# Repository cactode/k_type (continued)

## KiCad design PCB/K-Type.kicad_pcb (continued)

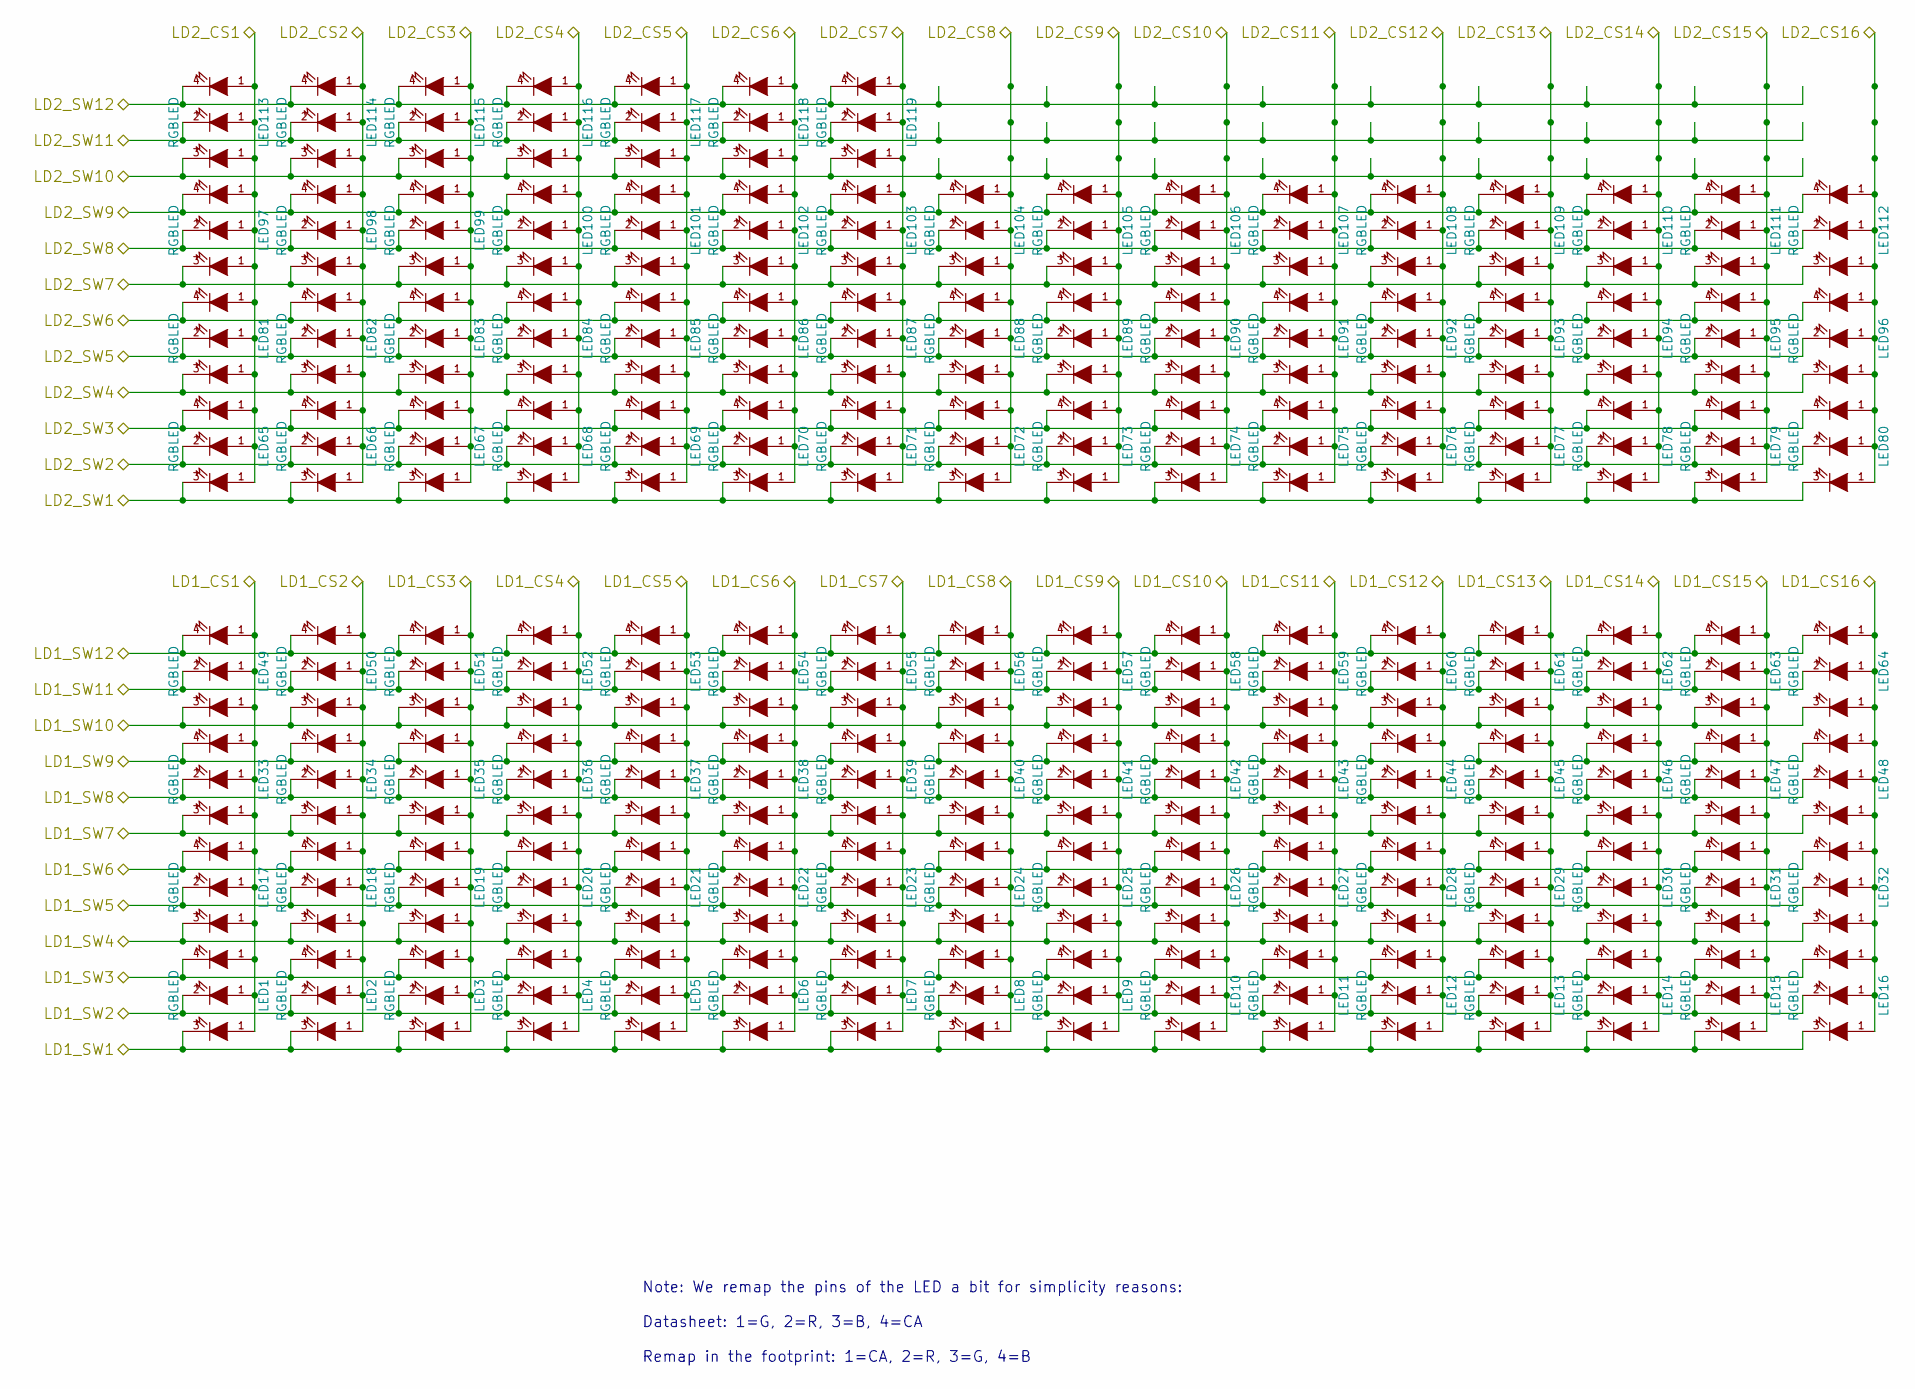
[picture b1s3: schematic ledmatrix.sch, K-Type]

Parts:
LED1, LED2, LED3, LED4, LED5, LED6, LED7, LED8, LED9, LED10, LED11, LED12, LED13, LED14, LED15, LED16, LED17, LED18, LED19, LED20, LED21, LED22, LED23, LED24, LED25, LED26, LED27, LED28, LED29, LED30, LED31, LED32, LED33, LED34, LED35, LED36, LED37, LED38, LED39, LED40, LED41, LED42, LED43, LED44, LED45, LED46, LED47, LED48, LED49, LED50, LED51, LED52, LED53, LED54, LED55, LED56, LED57, LED58, LED59, LED60, LED61, LED62, LED63, LED64, LED65, LED66, LED67, LED68, LED69, LED70, LED71, LED72, LED73, LED74, LED75, LED76, LED77, LED78, LED79, LED80, LED81, LED82, LED83, LED84, LED85, LED86, LED87: RGBLED; LED_RGB_3.2x2.8_REVMOUNT
LED88, LED89, LED90, LED91, LED92, LED93, LED94, LED95, LED96, LED97, LED98, LED99, LED100, LED101, LED102, LED103, LED104, LED105, LED106, LED107, LED108, LED109, LED110, LED111, LED112, LED113, LED114, LED115, LED116, LED117, LED118, LED119: RGBLED; LED_RGB_3.2x2.8_REVMOUNT_BACKWARDS

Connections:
/ledmatrix/LD1_CS1: LED1.1 (A), LED17.1 (A), LED33.1 (A), LED49.1 (A); also elsewhere on the board
/ledmatrix/LD1_CS2: LED2.1 (A), LED18.1 (A), LED34.1 (A), LED50.1 (A); also elsewhere on the board
/ledmatrix/LD1_CS3: LED3.1 (A), LED19.1 (A), LED35.1 (A), LED51.1 (A); also elsewhere on the board
/ledmatrix/LD1_CS4: LED4.1 (A), LED20.1 (A), LED36.1 (A), LED52.1 (A); also elsewhere on the board
/ledmatrix/LD1_CS5: LED5.1 (A), LED21.1 (A), LED37.1 (A), LED53.1 (A); also elsewhere on the board
/ledmatrix/LD1_CS6: LED6.1 (A), LED22.1 (A), LED38.1 (A), LED54.1 (A); also elsewhere on the board
/ledmatrix/LD1_CS7: LED7.1 (A), LED23.1 (A), LED39.1 (A), LED55.1 (A); also elsewhere on the board
/ledmatrix/LD1_CS8: LED8.1 (A), LED24.1 (A), LED40.1 (A), LED56.1 (A); also elsewhere on the board
/ledmatrix/LD1_CS9: LED9.1 (A), LED25.1 (A), LED41.1 (A), LED57.1 (A); also elsewhere on the board
/ledmatrix/LD1_CS10: LED10.1 (A), LED26.1 (A), LED42.1 (A), LED58.1 (A); also elsewhere on the board
/ledmatrix/LD1_CS11: LED11.1 (A), LED27.1 (A), LED43.1 (A), LED59.1 (A); also elsewhere on the board
/ledmatrix/LD1_CS12: LED12.1 (A), LED28.1 (A), LED44.1 (A), LED60.1 (A); also elsewhere on the board
/ledmatrix/LD1_CS13: LED13.1 (A), LED29.1 (A), LED45.1 (A), LED61.1 (A); also elsewhere on the board
/ledmatrix/LD1_CS14: LED14.1 (A), LED30.1 (A), LED46.1 (A), LED62.1 (A); also elsewhere on the board
/ledmatrix/LD1_CS15: LED15.1 (A), LED31.1 (A), LED47.1 (A), LED63.1 (A); also elsewhere on the board
/ledmatrix/LD1_CS16: LED16.1 (A), LED32.1 (A), LED48.1 (A), LED64.1 (A); also elsewhere on the board
/ledmatrix/LD1_SW1: LED1.3 (G), LED2.3 (G), LED3.3 (G), LED4.3 (G), LED5.3 (G), LED6.3 (G), LED7.3 (G), LED8.3 (G), LED9.3 (G), LED10.3 (G), LED11.3 (G), LED12.3 (G), LED13.3 (G), LED14.3 (G), LED15.3 (G), LED16.3 (G); also elsewhere on the board
/ledmatrix/LD1_SW2: LED1.2 (R), LED2.2 (R), LED3.2 (R), LED4.2 (R), LED5.2 (R), LED6.2 (R), LED7.2 (R), LED8.2 (R), LED9.2 (R), LED10.2 (R), LED11.2 (R), LED12.2 (R), LED13.2 (R), LED14.2 (R), LED15.2 (R), LED16.2 (R); also elsewhere on the board
/ledmatrix/LD1_SW3: LED1.4 (B), LED2.4 (B), LED3.4 (B), LED4.4 (B), LED5.4 (B), LED6.4 (B), LED7.4 (B), LED8.4 (B), LED9.4 (B), LED10.4 (B), LED11.4 (B), LED12.4 (B), LED13.4 (B), LED14.4 (B), LED15.4 (B), LED16.4 (B); also elsewhere on the board
/ledmatrix/LD1_SW4: LED17.3 (G), LED18.3 (G), LED19.3 (G), LED20.3 (G), LED21.3 (G), LED22.3 (G), LED23.3 (G), LED24.3 (G), LED25.3 (G), LED26.3 (G), LED27.3 (G), LED28.3 (G), LED29.3 (G), LED30.3 (G), LED31.3 (G), LED32.3 (G); also elsewhere on the board
/ledmatrix/LD1_SW5: LED17.2 (R), LED18.2 (R), LED19.2 (R), LED20.2 (R), LED21.2 (R), LED22.2 (R), LED23.2 (R), LED24.2 (R), LED25.2 (R), LED26.2 (R), LED27.2 (R), LED28.2 (R), LED29.2 (R), LED30.2 (R), LED31.2 (R), LED32.2 (R); also elsewhere on the board
/ledmatrix/LD1_SW6: LED17.4 (B), LED18.4 (B), LED19.4 (B), LED20.4 (B), LED21.4 (B), LED22.4 (B), LED23.4 (B), LED24.4 (B), LED25.4 (B), LED26.4 (B), LED27.4 (B), LED28.4 (B), LED29.4 (B), LED30.4 (B), LED31.4 (B), LED32.4 (B); also elsewhere on the board
/ledmatrix/LD1_SW7: LED33.3 (G), LED34.3 (G), LED35.3 (G), LED36.3 (G), LED37.3 (G), LED38.3 (G), LED39.3 (G), LED40.3 (G), LED41.3 (G), LED42.3 (G), LED43.3 (G), LED44.3 (G), LED45.3 (G), LED46.3 (G), LED47.3 (G), LED48.3 (G); also elsewhere on the board
/ledmatrix/LD1_SW8: LED33.2 (R), LED34.2 (R), LED35.2 (R), LED36.2 (R), LED37.2 (R), LED38.2 (R), LED39.2 (R), LED40.2 (R), LED41.2 (R), LED42.2 (R), LED43.2 (R), LED44.2 (R), LED45.2 (R), LED46.2 (R), LED47.2 (R), LED48.2 (R); also elsewhere on the board
/ledmatrix/LD1_SW9: LED33.4 (B), LED34.4 (B), LED35.4 (B), LED36.4 (B), LED37.4 (B), LED38.4 (B), LED39.4 (B), LED40.4 (B), LED41.4 (B), LED42.4 (B), LED43.4 (B), LED44.4 (B), LED45.4 (B), LED46.4 (B), LED47.4 (B), LED48.4 (B); also elsewhere on the board
/ledmatrix/LD1_SW10: LED49.3 (G), LED50.3 (G), LED51.3 (G), LED52.3 (G), LED53.3 (G), LED54.3 (G), LED55.3 (G), LED56.3 (G), LED57.3 (G), LED58.3 (G), LED59.3 (G), LED60.3 (G), LED61.3 (G), LED62.3 (G), LED63.3 (G), LED64.3 (G); also elsewhere on the board
/ledmatrix/LD1_SW11: LED49.2 (R), LED50.2 (R), LED51.2 (R), LED52.2 (R), LED53.2 (R), LED54.2 (R), LED55.2 (R), LED56.2 (R), LED57.2 (R), LED58.2 (R), LED59.2 (R), LED60.2 (R), LED61.2 (R), LED62.2 (R), LED63.2 (R), LED64.2 (R); also elsewhere on the board
/ledmatrix/LD1_SW12: LED49.4 (B), LED50.4 (B), LED51.4 (B), LED52.4 (B), LED53.4 (B), LED54.4 (B), LED55.4 (B), LED56.4 (B), LED57.4 (B), LED58.4 (B), LED59.4 (B), LED60.4 (B), LED61.4 (B), LED62.4 (B), LED63.4 (B), LED64.4 (B); also elsewhere on the board
/ledmatrix/LD2_CS1: LED65.1 (A), LED81.1 (A), LED97.1 (A), LED113.1 (A); also elsewhere on the board
/ledmatrix/LD2_CS2: LED66.1 (A), LED82.1 (A), LED98.1 (A), LED114.1 (A); also elsewhere on the board
/ledmatrix/LD2_CS3: LED67.1 (A), LED83.1 (A), LED99.1 (A), LED115.1 (A); also elsewhere on the board
/ledmatrix/LD2_CS4: LED68.1 (A), LED84.1 (A), LED100.1 (A), LED116.1 (A); also elsewhere on the board
/ledmatrix/LD2_CS5: LED69.1 (A), LED85.1 (A), LED101.1 (A), LED117.1 (A); also elsewhere on the board
/ledmatrix/LD2_CS6: LED70.1 (A), LED86.1 (A), LED102.1 (A), LED118.1 (A); also elsewhere on the board
/ledmatrix/LD2_CS7: LED71.1 (A), LED87.1 (A), LED103.1 (A), LED119.1 (A); also elsewhere on the board
/ledmatrix/LD2_CS8: LED72.1 (A), LED88.1 (A), LED104.1 (A); also elsewhere on the board
/ledmatrix/LD2_CS9: LED73.1 (A), LED89.1 (A), LED105.1 (A); also elsewhere on the board
/ledmatrix/LD2_CS10: LED74.1 (A), LED90.1 (A), LED106.1 (A); also elsewhere on the board
/ledmatrix/LD2_CS11: LED75.1 (A), LED91.1 (A), LED107.1 (A); also elsewhere on the board
/ledmatrix/LD2_CS12: LED76.1 (A), LED92.1 (A), LED108.1 (A); also elsewhere on the board
/ledmatrix/LD2_CS13: LED77.1 (A), LED93.1 (A), LED109.1 (A); also elsewhere on the board
/ledmatrix/LD2_CS14: LED78.1 (A), LED94.1 (A), LED110.1 (A); also elsewhere on the board
/ledmatrix/LD2_CS15: LED79.1 (A), LED95.1 (A), LED111.1 (A); also elsewhere on the board
/ledmatrix/LD2_CS16: LED80.1 (A), LED96.1 (A), LED112.1 (A); also elsewhere on the board
/ledmatrix/LD2_SW1: LED65.3 (G), LED66.3 (G), LED67.3 (G), LED68.3 (G), LED69.3 (G), LED70.3 (G), LED71.3 (G), LED72.3 (G), LED73.3 (G), LED74.3 (G), LED75.3 (G), LED76.3 (G), LED77.3 (G), LED78.3 (G), LED79.3 (G), LED80.3 (G); also elsewhere on the board
/ledmatrix/LD2_SW2: LED65.2 (R), LED66.2 (R), LED67.2 (R), LED68.2 (R), LED69.2 (R), LED70.2 (R), LED71.2 (R), LED72.2 (R), LED73.2 (R), LED74.2 (R), LED75.2 (R), LED76.2 (R), LED77.2 (R), LED78.2 (R), LED79.2 (R), LED80.2 (R); also elsewhere on the board
/ledmatrix/LD2_SW3: LED65.4 (B), LED66.4 (B), LED67.4 (B), LED68.4 (B), LED69.4 (B), LED70.4 (B), LED71.4 (B), LED72.4 (B), LED73.4 (B), LED74.4 (B), LED75.4 (B), LED76.4 (B), LED77.4 (B), LED78.4 (B), LED79.4 (B), LED80.4 (B); also elsewhere on the board
/ledmatrix/LD2_SW4: LED81.3 (G), LED82.3 (G), LED83.3 (G), LED84.3 (G), LED85.3 (G), LED86.3 (G), LED87.3 (G), LED88.3 (G), LED89.3 (G), LED90.3 (G), LED91.3 (G), LED92.3 (G), LED93.3 (G), LED94.3 (G), LED95.3 (G), LED96.3 (G); also elsewhere on the board
/ledmatrix/LD2_SW5: LED81.2 (R), LED82.2 (R), LED83.2 (R), LED84.2 (R), LED85.2 (R), LED86.2 (R), LED87.2 (R), LED88.2 (R), LED89.2 (R), LED90.2 (R), LED91.2 (R), LED92.2 (R), LED93.2 (R), LED94.2 (R), LED95.2 (R), LED96.2 (R); also elsewhere on the board
/ledmatrix/LD2_SW6: LED81.4 (B), LED82.4 (B), LED83.4 (B), LED84.4 (B), LED85.4 (B), LED86.4 (B), LED87.4 (B), LED88.4 (B), LED89.4 (B), LED90.4 (B), LED91.4 (B), LED92.4 (B), LED93.4 (B), LED94.4 (B), LED95.4 (B), LED96.4 (B); also elsewhere on the board
/ledmatrix/LD2_SW7: LED97.3 (G), LED98.3 (G), LED99.3 (G), LED100.3 (G), LED101.3 (G), LED102.3 (G), LED103.3 (G), LED104.3 (G), LED105.3 (G), LED106.3 (G), LED107.3 (G), LED108.3 (G), LED109.3 (G), LED110.3 (G), LED111.3 (G), LED112.3 (G); also elsewhere on the board
/ledmatrix/LD2_SW8: LED97.2 (R), LED98.2 (R), LED99.2 (R), LED100.2 (R), LED101.2 (R), LED102.2 (R), LED103.2 (R), LED104.2 (R), LED105.2 (R), LED106.2 (R), LED107.2 (R), LED108.2 (R), LED109.2 (R), LED110.2 (R), LED111.2 (R), LED112.2 (R); also elsewhere on the board
/ledmatrix/LD2_SW9: LED97.4 (B), LED98.4 (B), LED99.4 (B), LED100.4 (B), LED101.4 (B), LED102.4 (B), LED103.4 (B), LED104.4 (B), LED105.4 (B), LED106.4 (B), LED107.4 (B), LED108.4 (B), LED109.4 (B), LED110.4 (B), LED111.4 (B), LED112.4 (B); also elsewhere on the board
/ledmatrix/LD2_SW10: LED113.3 (G), LED114.3 (G), LED115.3 (G), LED116.3 (G), LED117.3 (G), LED118.3 (G), LED119.3 (G); also elsewhere on the board
/ledmatrix/LD2_SW11: LED113.2 (R), LED114.2 (R), LED115.2 (R), LED116.2 (R), LED117.2 (R), LED118.2 (R), LED119.2 (R); also elsewhere on the board
/ledmatrix/LD2_SW12: LED113.4 (B), LED114.4 (B), LED115.4 (B), LED116.4 (B), LED117.4 (B), LED118.4 (B), LED119.4 (B); also elsewhere on the board

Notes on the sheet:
Note: We remap the pins of the LED a bit for simplicity reasons: Datasheet: 1=G, 2=R, 3=B, 4=CA Remap in the footprint: 1=CA, 2=R, 3=G, 4=B

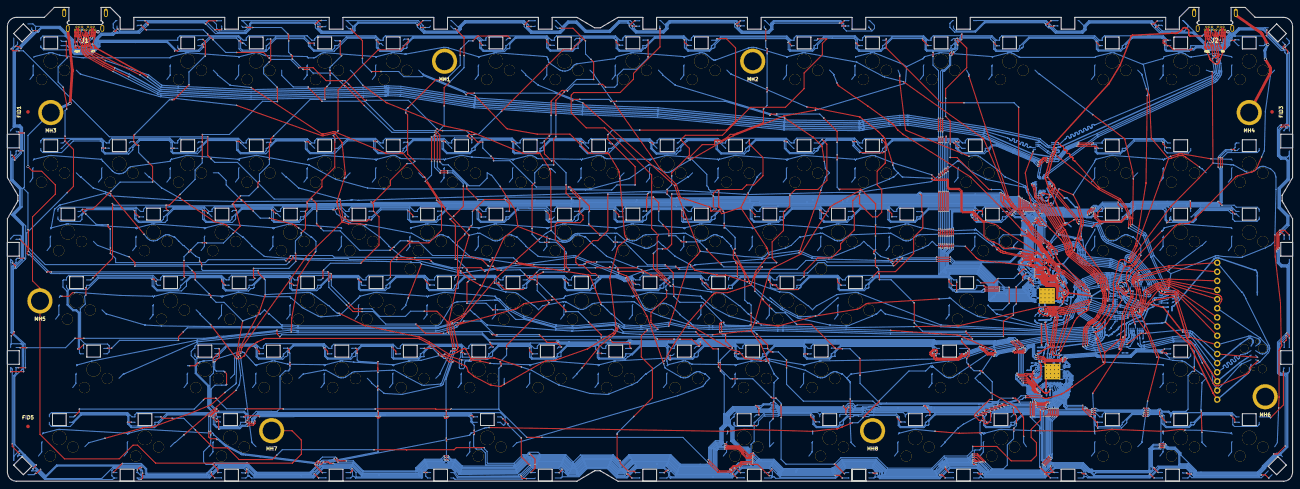
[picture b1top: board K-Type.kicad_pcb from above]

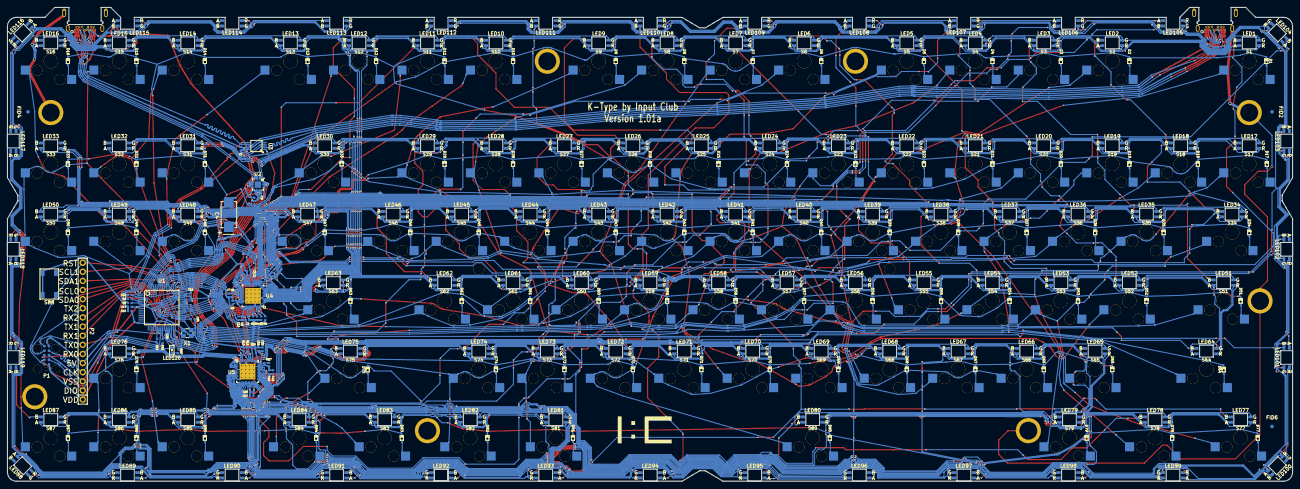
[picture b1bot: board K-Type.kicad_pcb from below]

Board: 2 copper layers, 357.5 x 131.8 mm, 362 parts (256 on the bottom side), 210 nets.

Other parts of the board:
FID1, FID2, FID3, FID4, FID5, FID6: >VALUE; FID
IC_LOGO: IC_LOGO
TH1, TH2: 1PAD; 1PAD-NPTH-SMALL

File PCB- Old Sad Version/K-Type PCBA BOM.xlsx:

# | Qty | Part Reference | Part Number | MFGR | Description | Footprint | Notes
1 | 12 | C5,C8,C11,C20,C23,C12,C2,C6,C9,C16,C18,C21 | EMK105B7104KV-F | Taiyo Yuden | Multilayer Ceramic Capacitors MLCC - SMD/SMT .1uF 16Volts X7R +/-10% 0402 STD | SMD-0402 | https://www.digikey.com/product-detail/en/EMK105B7104KV-F/58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
2 | 8 | C1,C3,C7,C10,C15,C17,C19,C22 | JMK105BJ474KV-F | Taiyo Yuden | Multilayer Ceramic Capacitors MLCC - SMD/SMT 0.47uF 6.3V X5R +/-10% 0402 Gen Pu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 | SMD-0402 | https://www.digikey.com/product-detail/en/JMK105BJ474KV-F/58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
3 | 1 | C4 | EEF-CX1D220R | Panasonic | Aluminum Organic Polymer Capacitors 22uF 20volt SP-Cap AEC-Q200 | SMD-7343-Pol | https://www.digikey.com/product-detail/en/EEF-CX1D220R/P1899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
4 | 2 | C14,C13 | JMK105C6225MV-F | Taiyo Yuden | Multilayer Ceramic Capacitors MLCC - SMD/SMT 2.2uF 6.3Volts X6S +/-20% 0402 STD | SMD-0402 | https://www.digikey.com/product-detail/en/taiyo-yuden/JMK105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
5 | 87 | D1..D87 | 1N4148X-TP | MCC | Diodes - General Purpose, Power, Switching 150mA 75V | SOD-523 | https://www.digikey.com/product-detail/en/1N4148X-TP/1N4148X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
6 | 2 | J2,J1 | DX07B024XJ1R1300 | JAE Electronics | USB Connectors HYBRID SMT/THRU-HOLE MID MNT - USB TYPE C | USB_C_MIDMOUNT_TH_IMPCUT | https://www.digikey.com/product-detail/en/DX07B024XJ1R1300/6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
7 | 87 | LED1..LED87 | KAILH-PG1280-SMT-LED | Kaihua or Hanhua | RGB LED - Reverse Mount | LED_RGB_3.2x2.8_REVMOUNT | https://www.aliexpress.com/item/Wholesale-100pcs-RGB-POWER-T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
8 | 32 | LED88..LED119 | KAILH-PG1280-SMT-LED | Kaihua or Hanhua | RGB LED - Reverse Mount | LED_RGB_3.2x2.8_REVMOUNT_BACKWARDS | https://www.aliexpress.com/item/Wholesale-100pcs-RGB-POWER-T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
9 | 1 | LED120 | LO Q976-PS-25 | Osram | Standard LEDs - SMD Orange, 605nm 280mcd, 20mA | LED-0603 | https://www.digikey.com/product-detail/en/osram-opto-semicon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
10 | 2 | R9,R17 | RK73B1ETTP133J | KOA Speer | Thick Film Resistors - SMD 1/16watts 13Kohms 5% | SMD-0402 | https://www.digikey.com/product-detail/en/koa-speer-electron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
11 | 4 | R8,R11,R7,R10 | RK73B1ETTP512J | KOA Speer | Thick Film Resistors - SMD 1/16watt 5.1Kohms 5% | SMD-0402 | https://www.digikey.com/product-detail/en/koa-speer-electron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
12 | 2 | R14,R15 | RK73B1ETTP101J | KOA Speer | Thick Film Resistors - SMD 1/16watts 100ohms 5% | SMD-0402 | https://www.digikey.com/product-detail/en/koa-speer-electron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
13 | 2 | R2,R1 | RK73B1ETTP330J | KOA Speer | Thick Film Resistors - SMD 1/16watts 33ohms 5% | SMD-0402 | https://www.digikey.com/product-detail/en/RK73B1ETTP330J/201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
14 | 5 | R3,R4,R12,R13,R16 | RK73B1ETTP102J | KOA Speer | Thick Film Resistors - SMD 1/16watts 1Kohms 5% | SMD-0402 | https://www.digikey.com/product-detail/en/koa-speer-electron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
15 | 2 | R5,R6 | RK73B1ETTP104J | KOA Speer | Thick Film Resistors - SMD 1/16watt 100Kohms 5% | SMD-0402 | https://www.digikey.com/product-detail/en/koa-speer-electron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
16 | 87 | S1..S87 | CPG151101S11 | Kaihua | Switch Socket - SMD | SW_SOCKET_COMBINED | https://kbdfans.cn/products/mechanical-keyboard-switches-kai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
17 | 1 | S88 | SKQGAKE010 | ALPS | Tactile Switches 50 mAmps at 12 Volts | TACT_5.2x5.2
18 | 1 | U1 | MK20DX256VLH7 | NXP / Freescale | ARM Microcontrollers - MCU KINETIS 256K | LQFP64 | https://www.digikey.com/products/en?keywords=MK20DX256VLH7
19 | 1 | U2 | TS3DS10224RUKR | Texas Instruments | Multiplexer Switch ICs High-Speed 2:4 Diff Mux/Demux | QFN_20_0.4 | https://www.digikey.com/product-detail/en/texas-instruments/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
20 | 1 | U3 | TS3USB30EDGSR | Texas Instruments | USB Switch ICs High-Speed USB 2.0 1:2 Mux/Demux Switch | VSSOP-10 | https://www.digikey.com/product-detail/en/texas-instruments/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
21 | 2 | U4,U5 | IS31FL3733 | ISSI | 12x16 DOTS MATRIX LED DRIVER, QFN-48 | QFN-48-1EP-6mm | https://www.digikey.com/product-detail/en/IS31FL3733-QFLS4-T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
22 | 1 | X1 | NX3225SA-16.000M-STD-CSR-1 | NDK | CRYSTAL 16.0000MHZ 8PF SMD | DFN_3.2x2.5 | https://www.digikey.com/product-detail/en/NX3225SA-16.000M-S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

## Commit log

2019-05-21 Changed footprints
2019-05-21 Recorded state of DRC before changes
2019-05-21 Updated footprints; everything is broken now.
2019-05-21 Removed bad traces; gotta redraw everything now
2019-05-25 Making slow, painful progress
2019-05-25 Making more, slow, painful progress
2019-05-25 Saving before more work
2019-05-25 Preparing to use autorouter?
2019-05-27 Adding newer attempt at PCB
2019-05-27 Halfway done?
2019-05-27 Saving progress
2019-05-27 All RGB traces routed
2019-05-28 Finished routing interboard connections
2019-05-28 All traces except for cross traces routed
2019-05-28 Adding final cross traces
2019-05-28 add more traces
2019-05-30 Added some more traces
2019-06-02 Mechanical Stuff
2019-06-02 Fixing merge conflicts like a god
2019-06-02 About to do the dumb thing
